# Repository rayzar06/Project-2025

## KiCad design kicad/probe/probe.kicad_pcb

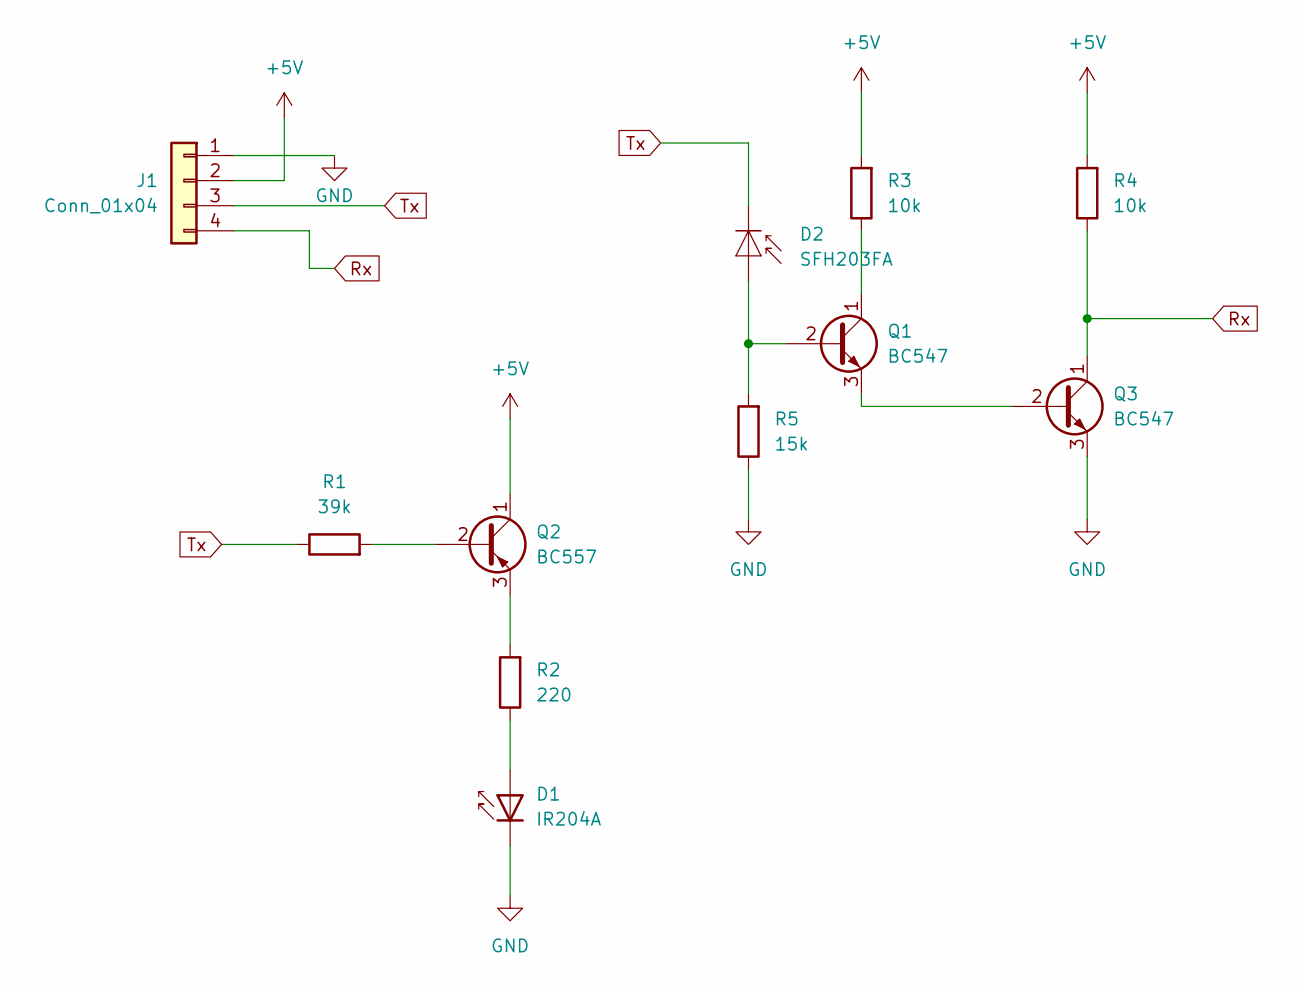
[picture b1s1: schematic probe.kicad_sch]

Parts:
D1: IR204A; LED_D5.0mm_IRGrey
D2: SFH203FA; LED_D5.0mm_IRGrey
J1: Conn_01x04; PinHeader_1x04_P2.54mm_Vertical
Q1, Q3: BC547; TO-92_Inline
Q2: BC557; TO-92_Inline
R1: 39k; R_Axial_DIN0204_L3.6mm_D1.6mm_P7.62mm_Horizontal
R2: 220; R_Axial_DIN0204_L3.6mm_D1.6mm_P7.62mm_Horizontal
R3, R4: 10k; R_Axial_DIN0204_L3.6mm_D1.6mm_P7.62mm_Horizontal
R5: 15k; R_Axial_DIN0204_L3.6mm_D1.6mm_P7.62mm_Horizontal

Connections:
+5V: J1.2, Q2.1 (C), R3.2, R4.2
GND: D1.1 (K), J1.1, Q3.3 (E), R5.1
unnamed: D1.2 (A), R2.1
unnamed: D2.2 (A), Q1.2 (B), R5.2
unnamed: Q1.1 (C), R3.1
unnamed: Q1.3 (E), Q3.2 (B)
unnamed: Q2.2 (B), R1.2
unnamed: Q2.3 (E), R2.2
Rx: J1.4, Q3.1 (C), R4.1
Tx: D2.1 (K), J1.3, R1.1

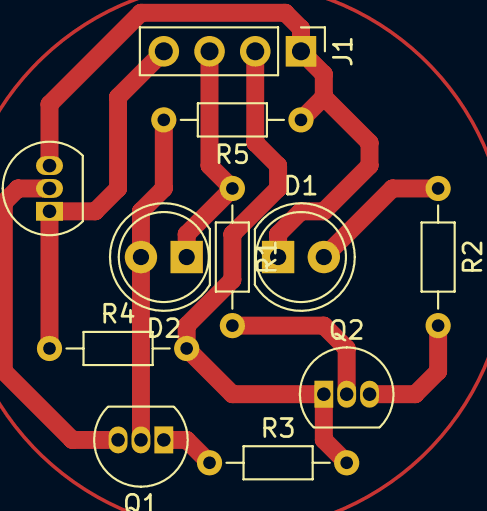
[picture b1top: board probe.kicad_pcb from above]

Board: 2 copper layers, 11 parts (0 on the bottom side), 10 nets.

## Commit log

2024-07-29 added papers
2024-07-29 added more papers
2024-07-29 new paper added
2024-07-29 ev paper
2024-07-29 our project paper
2024-07-29 new paper
2024-07-29 dhusb
2024-08-05 zeroth presentation
2024-08-05 zero
2024-11-01 added modules
2024-11-02 sim files added
